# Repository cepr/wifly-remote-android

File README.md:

wifly-remote-android
====================

Garage door remote control for Android using a Roving Network WiFly module.

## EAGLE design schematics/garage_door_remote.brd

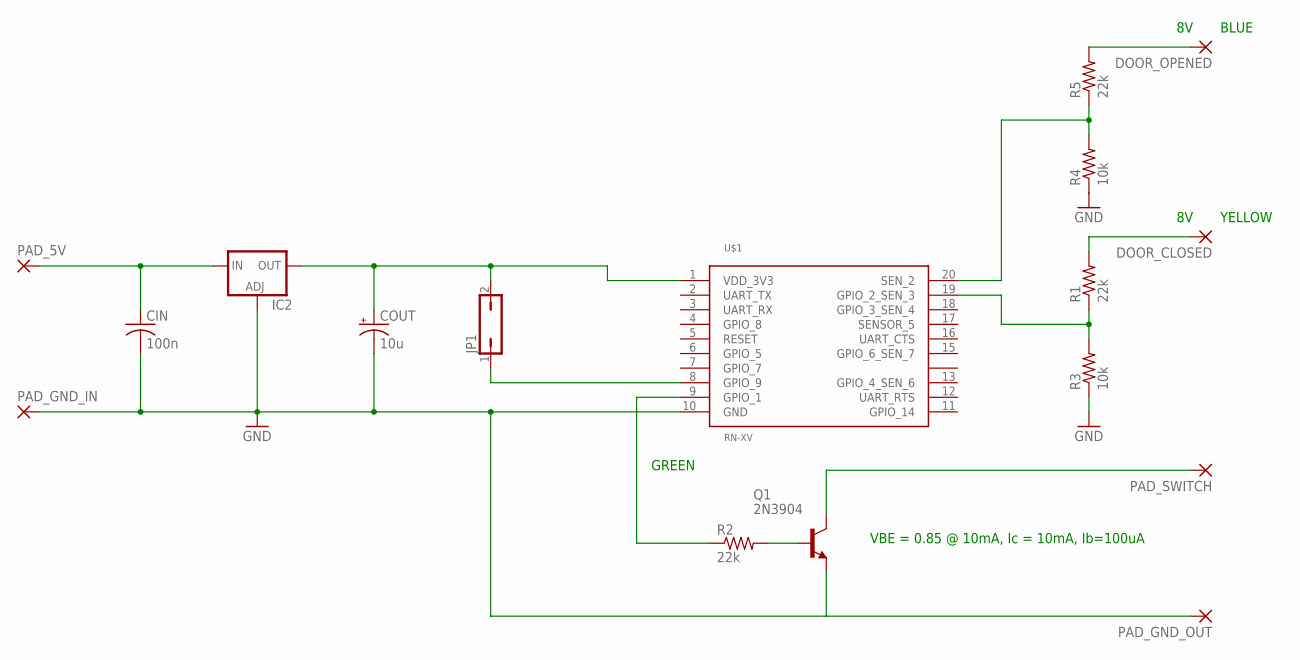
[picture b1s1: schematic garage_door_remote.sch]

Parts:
CIN: 100n; C025-024X044
COUT: 10u; E2,5-6E
DOOR_CLOSED: 2,54/1,0
DOOR_OPENED: 2,54/1,0
IC2: LM317TS; 317TS
JP1: JP1Q; JP1
PAD_5V: 2,54/1,0
PAD_GND_IN: 2,54/1,0
PAD_GND_OUT: 2,54/1,0
PAD_SWITCH: 2,54/1,0
Q1: 2N3904; TO92
R1, R2: 22k; 0207/12
R3: 10k; 0207/12
R4: 10k; 0204V
R5: 22k; 0204V
U$1: RN-XV

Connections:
GND: CIN.2, COUT.-, IC2.1 (ADJ), PAD_GND_IN.1, PAD_GND_OUT.1, Q1.3 (E), R3.1, R4.1, U$1.10 (GND)
unnamed: JP1.1, U$1.8 (GPIO_9)
unnamed: COUT.+, IC2.2 (OUT), JP1.2, U$1.1 (VDD_3V3)
unnamed: Q1.2 (B), R2.2
unnamed: R1.1, R3.2, U$1.19 (GPIO_2_SEN_3)
unnamed: R4.2, R5.1, U$1.20 (SEN_2)
unnamed: R2.1, U$1.9 (GPIO_1)
unnamed: PAD_SWITCH.1, Q1.1 (C)
unnamed: CIN.1, IC2.3 (IN), PAD_5V.1
unnamed: DOOR_OPENED.1, R5.2
unnamed: DOOR_CLOSED.1, R1.2

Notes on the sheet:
VBE = 0.85 @ 10mA, Ic = 10mA, Ib=100uA
GREEN
BLUE
YELLOW

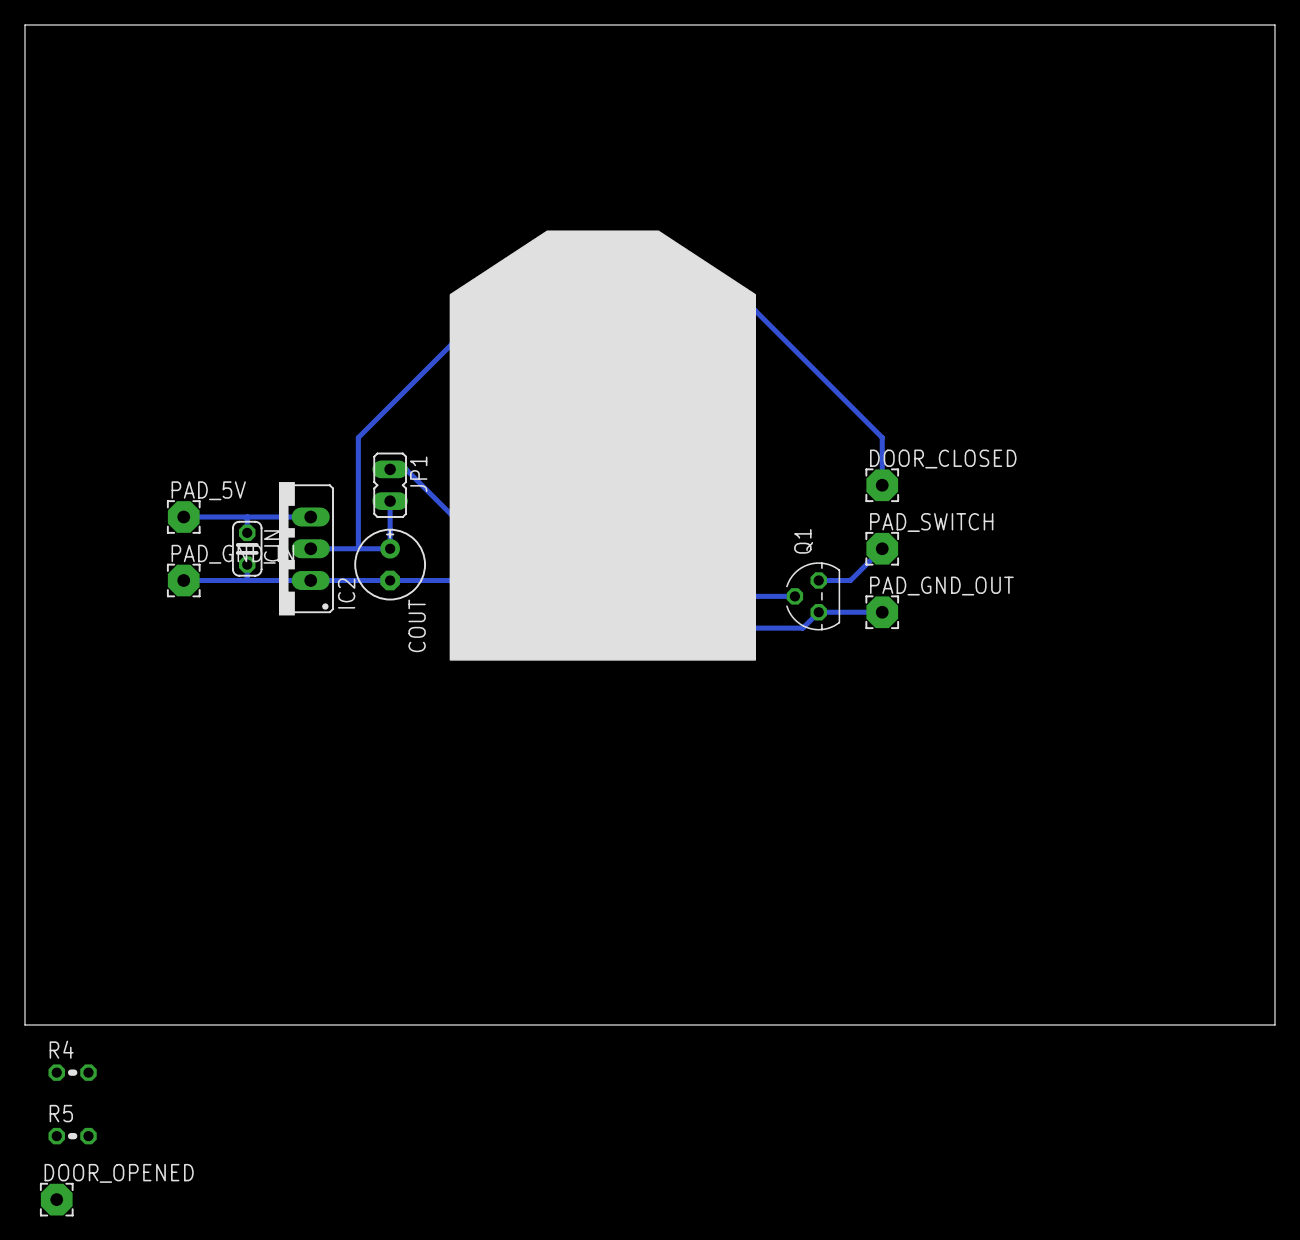
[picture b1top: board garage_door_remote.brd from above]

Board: 2 copper layers, 100.0 x 80.0 mm, 17 parts (0 on the bottom side), 11 nets.

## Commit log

2014-03-31 Version 1.0
2014-03-31 Adding schematics
